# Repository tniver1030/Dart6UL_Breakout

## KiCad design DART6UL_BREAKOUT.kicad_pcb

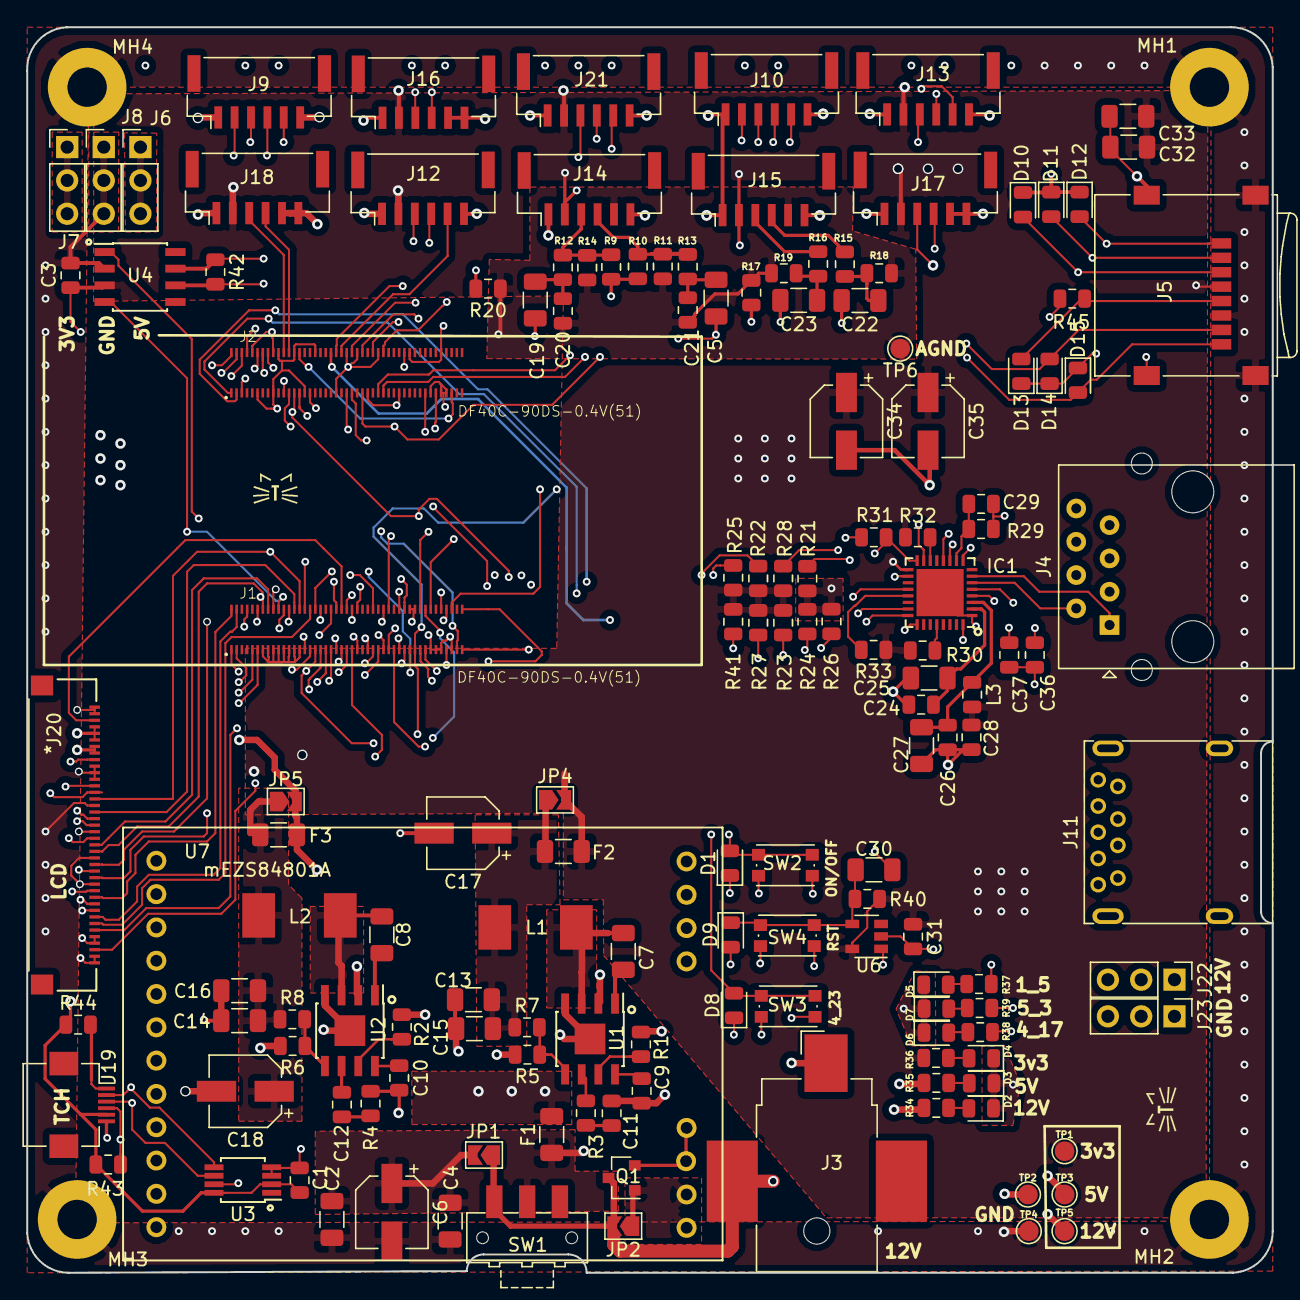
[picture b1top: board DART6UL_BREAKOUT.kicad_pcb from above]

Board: 4 copper layers, 95.0 x 95.0 mm, 152 parts (0 on the bottom side), 140 nets.

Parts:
C1: 10uF; C_0805_2012Metric
C2, C13, C14, C32: 0.1uF; C_1206_3216Metric
C3, C24, C26, C28, C36, C37: 100nF; C_0805_2012Metric
C4, C5, C19, C22, C23, C30: 10uF; C_1206_3216Metric
C6, C17, C18, C34, C35: 47; CP_Elec_5x5.3
C7, C8: 10nF; C_1206_3216Metric
C9, C10: .1uF; C_0805_2012Metric
C11, C12: 3.9nF; C_0805_2012Metric
C15, C16, C33: 22uF; C_1206_3216Metric
C20, C21: 200pF; C_0805_2012Metric
C25, C27: 2.2uF; C_1206_3216Metric
C29: 1nF; C_0805_2012Metric
C31: 1uF; C_0805_2012Metric
D1, D8, D9, D10, D11, D12, D13, D14, D15: D_TVS; D_0805_2012Metric
D2, D3, D4, D5, D6, D7: LED; LED_0805_2012Metric
F1, F2, F3: Fuse; Fuse_1206_3216Metric
IC1: KSZ8051RNL; QFN-32-1EP_5x5mm_P0.5mm_EP3.6x3.6mm
J1, J2: DF40C-90DS-0.4V(51); HIROSE_DF40C-90DS-0.4V(51)
J3: Barrel_Jack; BarrelJack_CUI_PJ-036AH-SMT_Horizontal
J4: RJ45; ARJ11G-MBSD-LU2-ND
J5: Micro_SD_Card; microSD_HC_Wuerth_693072010801
J6, J7, J8, J22, J23: Conn_01x03_Female; PinHeader_1x03_P2.54mm_Vertical
J9, J10, J12, J13, J14, J15, J16, J17, J18, J21: Conn_01x06_Male; JST_GH_BM06B-GHS-TBT_1x06-1MP_P1.25mm_Vertical
J11: Conn_01x06_Male; USB3_A_Molex_48393-001
J19: Conn_01x06_Female; Hirose_FH12-6S-0.5SH_1x06-1MP_P0.50mm_Horizontal
J20: Conn_01x40_Female; XF2M-4015-1A
JP1, JP2, JP4, JP5: SolderJumper_2_Open; SolderJumper-2_P1.3mm_Open_TrianglePad1.0x1.5mm
L1, L2: 10uH-4A1; Inductor_SMD
L3: 122R 1.3A; L_0805_2012Metric
MH1, MH2, MH3, MH4: MountingHole_Pad; MountingHole_3mm_Pad
Q1: BS250; SOT-23
R1, R2: R100K; R_0805_2012Metric
R3, R4: 6.8k; R_0805_2012Metric
R5, R6: 10k 1%; R_0805_2012Metric
R7: 26.1k 1%; R_0805_2012Metric
R8: 44.2k 1%; R_0805_2012Metric
R9, R10: 2.2k 1%; R_0805_2012Metric
R11, R12, R13, R14: 5.6k 1%; R_0805_2012Metric
R15, R16: 100; R_0805_2012Metric
R17, R20: 0; R_0805_2012Metric
R18, R19: 47K; R_0805_2012Metric
R21, R30, R31, R32, R43, R44: 10K; R_0805_2012Metric
R22, R23, R24, R25, R26, R27, R28, R41: 10k; R_0805_2012Metric
R29: 6.49K; R_0805_2012Metric
R33: 1K; R_0805_2012Metric
R34, R35, R36, R37, R38, R39: 500; R_0805_2012Metric
R40: 510; R_0805_2012Metric
R42: DNP; R_0805_2012Metric
R45: 22R 1%; R_0805_2012Metric
SW1: SW_SPST; SW_SPDT_CK-JS102011SAQN
SW2, SW3, SW4: SW_Push; SW_SPST_KMR2
TP1, TP2, TP3, TP4, TP5, TP6: TestPoint; TestPoint_Pad_D1.5mm
U1, U2: MP2307; SOIC-8-1EP_3.9x4.9mm_P1.27mm_EP2.35x2.35mm
U3: BR24G04-3; MSOP-8_3x3mm_P0.65mm
U4: SN65HVD232; SOIC-8_3.9x4.9mm_P1.27mm
U6: MIC2775; SOT-23-5
U7: mEZS84801A

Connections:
3V3DC: C1.1, C3.1, C28.1, C31.1, C32.1, C33.1, C34.1, C35.1, F2.2, IC1.17, J1.13, J1.15, J1.17, J1.19, J1.21, J1.23, J1.25, J1.27, J2.23, J5.4, J7.1, J7.2, J7.3, J12.2, J13.2, J14.2, J15.2, J16.2, J17.2, J18.2, J19.5, J20.7, J20.8, J21.2, JP4.2, L3.2, R22.1, R23.1, R25.1, R27.1, R28.1, R30.1, R32.1, R33.1, R36.2, R40.1, R41.1, R43.1, R44.1, TP1.1, U3.2, U3.8, U4.3, U6.5
5VDC: F3.2, J6.1, J6.2, J6.3, J9.1, J10.1, J12.1, J13.1, J14.1, J15.1, J16.1, J17.1, J18.1, J20.4, J20.5, J20.6, J21.1, JP5.2, R35.2, TP3.1
12VDC: C2.1, C4.1, C6.1, F1.2, JP1.2, R34.2, SW1.2, TP5.1
/AUDIO0: C22.2, J2.12
/AUDIO1: C23.2, J2.16
/AUDIO2: J2.14, R17.2
/AUDIO3: J2.6, R9.1, R10.1
/AUDIO4: C5.2, J2.2
/AUDIO5: C19.2, J2.4
/CAN_CPU0: J1.22, R25.2, U4.1
/CAN_CPU1: J1.20, U4.4
/CAN_OUT0: J16.3, R42.1, U4.7
/CAN_OUT1: J16.4, R42.2, U4.6
/CONNECTORS/12VDC: J3.2, J22.1, J22.2, J22.3, JP1.1, JP2.2, Q1.3, SW1.1
/CONNECTORS/E10: J1.11, U7.5
/CONNECTORS/E11: J1.9, U7.6
/CONNECTORS/E12: J1.3, U7.7
/CONNECTORS/E15: J1.1, U7.10
/CONNECTORS/E_CONN0: IC1.7, J4.1
/CONNECTORS/E_CONN1: IC1.6, J4.2
/CONNECTORS/E_CONN2: C36.1, J4.3
/CONNECTORS/E_CONN5: C37.1, J4.6
/CONNECTORS/E_CONN6: IC1.5, J4.7
/CONNECTORS/E_CONN7: IC1.4, J4.8
/CONNECTORS/GPIO_EXT11: J2.8, J13.4
/CONNECTORS/GPIO_EXT21: J1.62, J12.4
/CONNECTORS/I2C10: J2.24, J18.4
/CONNECTORS/I2C11: J2.22, J18.3
/CONNECTORS/LCD0: J1.49, J20.38
/CONNECTORS/LCD1: J1.8, J20.35
/CONNECTORS/LCD2: J1.32, J20.34
/CONNECTORS/LCD3: J1.4, J20.33
/CONNECTORS/LCD4: J1.47, J20.31
/CONNECTORS/LCD5: J1.2, J20.30
/CONNECTORS/LCD6: J1.33, J20.29
/CONNECTORS/LCD7: J1.46, J20.27
/CONNECTORS/LCD8: J1.73, J20.26, R26.2
/CONNECTORS/LCD9: J1.18, J20.25
/CONNECTORS/LCD10: J1.14, J20.23, R27.2
/CONNECTORS/LCD11: J1.16, J20.22
/CONNECTORS/LCD12: J1.34, J20.21
/CONNECTORS/LCD13: J1.75, J20.19
/CONNECTORS/LCD14: J1.40, J20.18
/CONNECTORS/LCD15: J1.26, J20.17
/CONNECTORS/LCD16: J1.28, J20.15, R22.2
/CONNECTORS/LCD17: J1.30, J20.14, R23.2
/CONNECTORS/LCD18: J1.42, J20.13, R24.2
/CONNECTORS/LCD19: J1.50, J20.9
/CONNECTORS/LCD20: J1.44, J20.3
/CONNECTORS/SDCARD6: J1.89, R41.2
/CONNECTORS/UART20: J1.61, J9.2
/CONNECTORS/UART21: J1.69, J9.3
/CONNECTORS/UART22: J1.59, J9.4
/CONNECTORS/UART23: J1.67, J9.5
/CONNECTORS/USB0: J2.40, J11.1
/CONNECTORS/USB1: J2.1, J11.2
/CONNECTORS/USB2: J2.3, J11.3
/ETHERNET_PHY/E20: IC1.16, J1.37, R31.1
/ETHERNET_PHY/E21: IC1.15, J1.39
/ETHERNET_PHY/E22: IC1.24, J1.43
/ETHERNET_PHY/E23: IC1.25, J1.35
/ETHERNET_PHY/E24: IC1.18, J1.31
/ETHERNET_PHY/E25: IC1.20, J1.55
/ETHERNET_PHY/E26: IC1.23, J1.45
/ETHERNET_PHY/E27: IC1.9, J1.57
/ETHERNET_PHY/E28: IC1.11, J2.75
/ETHERNET_PHY/E29: IC1.12, J2.79
/ETHERNET_PHY/E210: IC1.32, J2.21
/HP_OUT0: J15.4, R15.1
/HP_OUT1: J15.3, R16.1
/I2C20: J2.68, J17.3, J19.3, U3.6
/I2C21: J1.71, J17.4, J19.2, U3.5
/LCD_T: J1.56, J19.4, R43.2
/MIC_IN0: J14.4, R10.2, R11.2, R13.1
/MIC_IN1: J14.3, R9.2, R12.2, R14.1
/ONOFF: D1.2, J2.45, SW2.1
/SOM_BREAKOUT/BOOT1: J2.31, R28.2
/SOM_BREAKOUT/DEBUG_UART_CTS_B: J2.57, J10.5
/SOM_BREAKOUT/DEBUG_UART_RTS_B: J2.51, J10.3, R21.1
/SOM_BREAKOUT/DEBUG_UART_RX: J2.59, J10.2
/SOM_BREAKOUT/DEBUG_UART_TX: J2.56, J10.4
/SOM_BREAKOUT/GPIO1_0: J2.60, J13.5
/SOM_BREAKOUT/GPIO1_1: J2.44, J12.5
/SOM_BREAKOUT/GPIO1_2: J2.48, J21.5
/SOM_BREAKOUT/GPIO1_4: J2.52, J21.3
/SOM_BREAKOUT/GPIO1_5: J2.27, R37.2
/SOM_BREAKOUT/GPIO1_9: J2.42, J21.4
/SOM_BREAKOUT/GPIO4_17: J1.76, R38.2
/SOM_BREAKOUT/GPIO4_20: J1.86, J13.3
/SOM_BREAKOUT/GPIO4_23: D8.2, J1.90, SW3.1
/SOM_BREAKOUT/GPIO4_24: J1.87, J12.3
/SOM_BREAKOUT/GPIO5_3: J1.63, R39.2
/SOM_BREAKOUT/OSC_32K: J2.28, J2.85
/SOM_BREAKOUT/POR: J2.47, U6.1
/SOM_BREAKOUT/RESET0: C30.1, J2.25
/SOM_BREAKOUT/SD1_CLK: J1.83, R45.2
/SOM_BREAKOUT/SD1_CMD: D10.2, J1.82, J5.3
/SOM_BREAKOUT/SD1_DATA0: D14.2, J1.68, J5.7
/SOM_BREAKOUT/SD1_DATA1: D15.2, J1.74, J5.8
/SOM_BREAKOUT/SD1_DATA2: D12.2, J1.78, J5.1
/SOM_BREAKOUT/SD1_DATA3: D11.2, J1.66, J5.2
/Voltage_Regulation/V_IN: F1.1, R1.2, R2.2, U1.2, U2.2
AGND: C20.2, C21.2, J2.10, J2.18, J14.5, J15.5, R13.2, R14.2, R17.1, R18.2, R19.2, R20.1, TP6.1
GND: C1.2, C2.2, C3.2, C4.2, C6.2, C9.2, C10.2, C13.2, C14.2, C15.2, C16.2, C17.2, C18.2, C24.2, C25.2, C26.2, C27.2, C28.2, C29.2, C31.2, C32.2, C33.2, C34.2, C35.2, C36.2, C37.2, D1.1, D2.1, D3.1, D4.1, D5.1, D6.1, D7.1, D8.1, D9.2, D10.1, D11.1, D12.1, D13.1, D14.1, D15.1, IC1.1, IC1.33, J1.12, J1.24, J1.29, J1.36, J1.41, J1.48, J1.53, J1.60, J1.65, J1.70, J1.72, J1.77, J1.79, J1.81, J1.84, J1.85, J2.5, J2.11, J2.17, J2.20, J2.26, J2.29, J2.34, J2.41, J2.46, J2.50, J2.53, J2.58, J2.65, J2.70, J2.77, J2.81, J2.82, J2.83, J3.1, J5.6, J5.9, J8.1, J8.2, J8.3, J9.6, J10.6, J11.4, J12.6, J13.6, J14.6, J15.6, J16.5, J16.6, J17.5, J17.6, J18.5, J18.6, J19.6, J20.1, J20.2, J20.10, J20.11, J20.12, J20.16, J20.20, J20.24, J20.28, J20.32, J20.36, J20.37, J20.39, J20.40, J21.6, J23.1, J23.2, J23.3, MH1.1, MH2.1, MH3.1, MH4.1, Q1.2, R3.2, R4.2, R5.2, R6.2, R20.2, R21.2, R24.1, R26.1, R29.2, R31.2, SW2.2, SW3.2, SW4.1, TP2.1, TP4.1, U1.4, U1.9, U2.4, U2.9, U3.3, U3.4, U3.7, U4.2, U6.2, U7.15, U7.16
unnamed: C13.1, C15.1, C17.1, F2.1, JP4.1, L1.1, R7.1
unnamed: C14.1, C16.1, C18.1, F3.1, JP5.1, L2.1, R8.1
unnamed: C7.1, U1.1
unnamed: C7.2, L1.2, U1.3
unnamed: C8.1, U2.1
unnamed: C8.2, L2.2, U2.3
unnamed: C9.1, U1.8
unnamed: C10.1, U2.8
unnamed: C11.1, U1.6
unnamed: C11.2, R3.1
unnamed: C12.1, U2.6
unnamed: C12.2, R4.1
unnamed: C19.1, C20.1, R12.1
unnamed: C5.1, C21.1, R11.1
unnamed: C22.1, R15.2, R18.1
unnamed: C23.1, R16.2, R19.1
unnamed: C24.1, C25.1, IC1.2
unnamed: C26.1, C27.1, IC1.3, L3.1
unnamed: C29.1, IC1.10, R29.1
unnamed: C30.2, D9.1, R40.2, SW4.2, U6.4
unnamed: D2.2, R34.1
unnamed: D3.2, R35.1
unnamed: D4.2, R36.1
unnamed: D5.2, R37.1
unnamed: D6.2, R38.1
unnamed: D7.2, R39.1
unnamed: D13.2, J5.5, R45.1
unnamed: IC1.14, R32.2
unnamed: IC1.21, R33.2
unnamed: IC1.28, R30.2
unnamed: J19.1, R44.2
unnamed: JP2.1, Q1.1, U7.13, U7.14
unnamed: R1.1, U1.7
unnamed: R2.1, U2.7
unnamed: R5.1, R7.2, U1.5
unnamed: R6.1, R8.2, U2.5

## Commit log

2019-05-07 Init Commit

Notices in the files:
parts and their libraries:
Copyright 2016 Accelerated Designs. All rights reserved.
